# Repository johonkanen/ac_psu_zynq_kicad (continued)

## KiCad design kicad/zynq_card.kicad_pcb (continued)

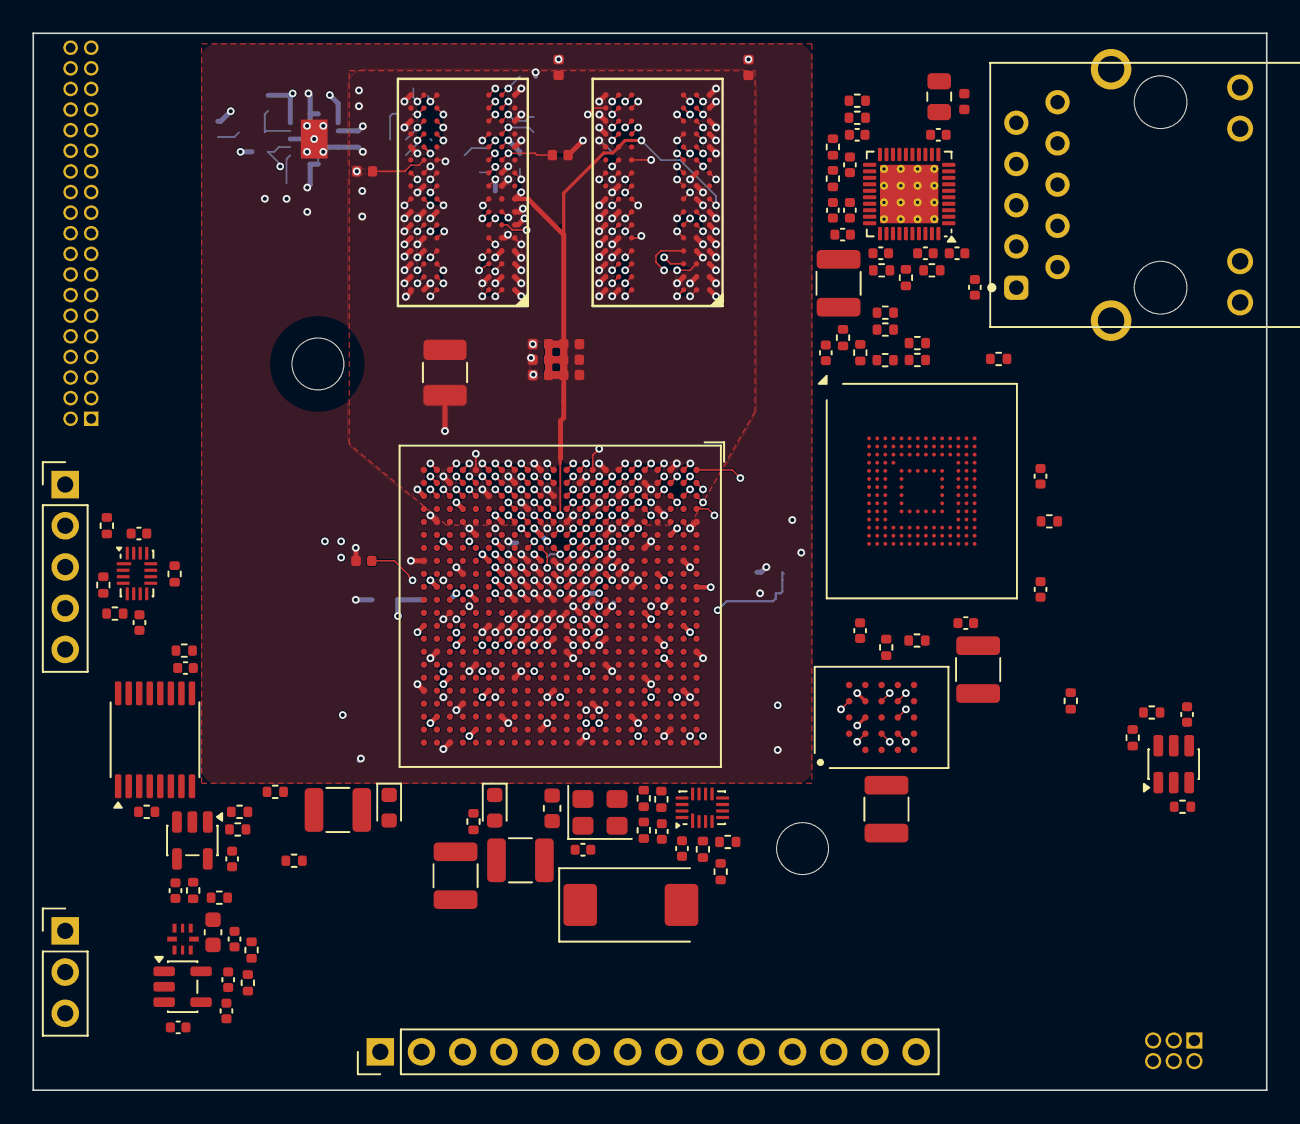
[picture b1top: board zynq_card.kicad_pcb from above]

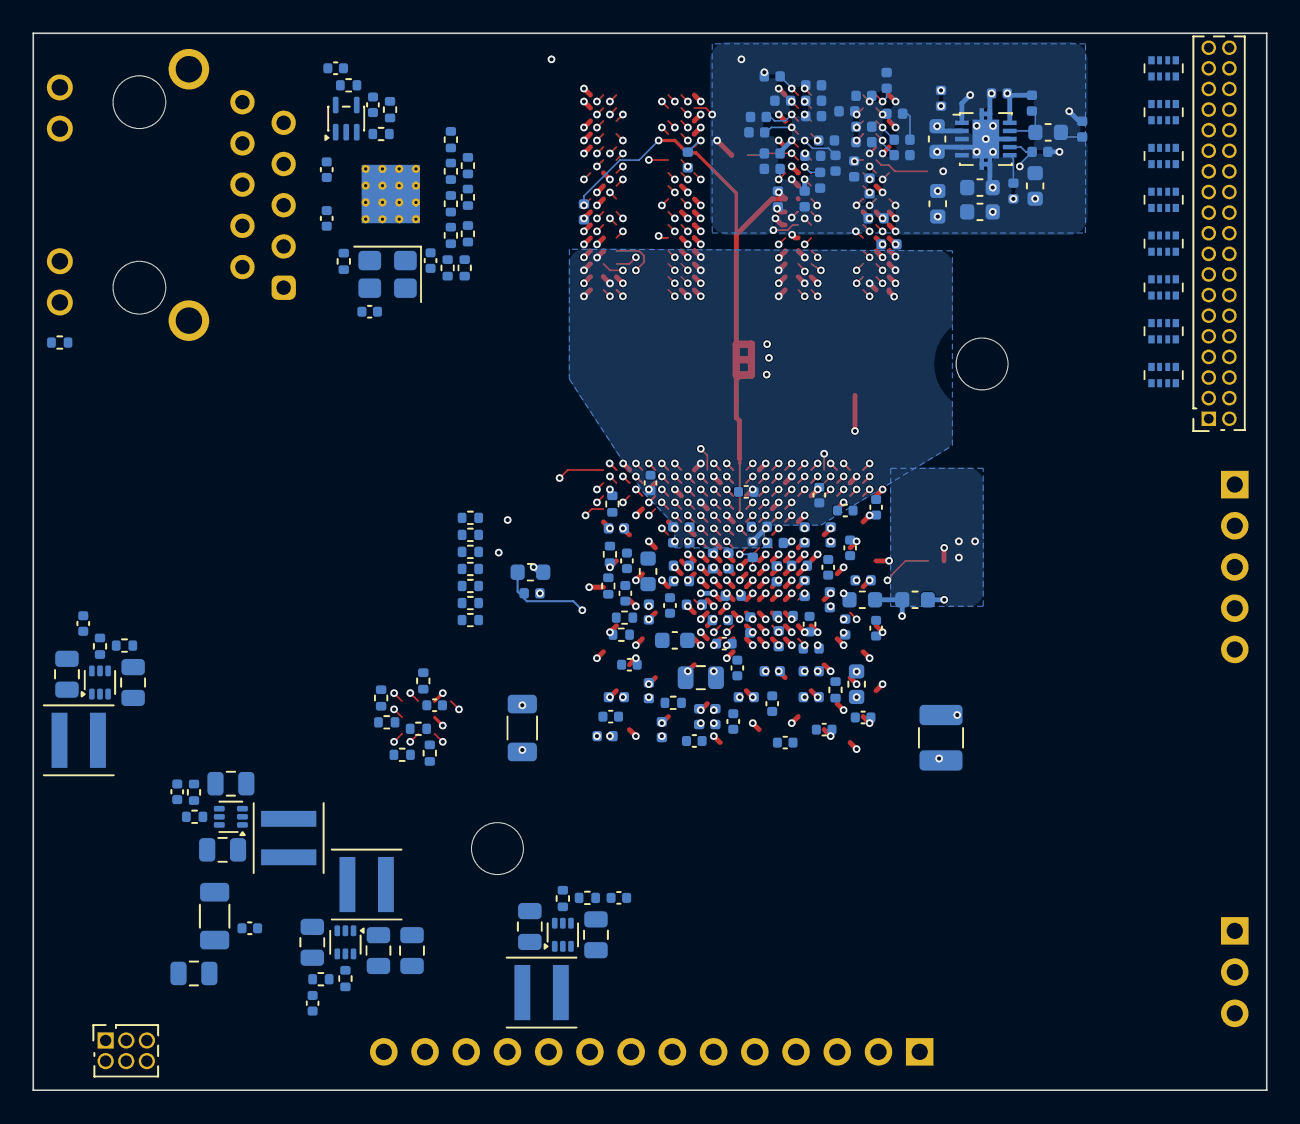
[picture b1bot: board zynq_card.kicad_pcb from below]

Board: 8 copper layers, 76.0 x 65.1 mm, 311 parts (195 on the bottom side), 262 nets.

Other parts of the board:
H1, H2: MountingHole_3.2mm_M3

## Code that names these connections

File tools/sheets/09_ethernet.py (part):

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Ported from the Ti135 card (efinix_soc_board/tools/sheets/09_ethernet.py): same circuit, parts and refs. Checked
against the Realtek RTL8211F(I)/FD(I) data sheet Rev. 1.7:
- One 3.3 V supply. LDO_OUT (pin 30, FD(I) = LDO, no inductor) feeds only AVDD10/DVDD10, caps only.
- RGMII and MDIO pads run from the internal pad LDO at 1.8 V: CFG_EXT (LED0) = 0, CFG_LDO[1:0] (LED2, LED1) = 10
  (Table 6, Table 11). DVDD_RG (pin 28) is that LDO's output: caps only. Both MIO banks are 1.8 V, so the RGMII
  levels match: PHY Vih(1.8 V) 1.2 V vs HSTL 1.8 V VOH; PHY Voh >= 0.9 x 1.8 V vs the HSTL receivers on
  PS_MIO_VREF 0.9 V (sheet 6). Table 58: MDIO also runs at the RGMII pad voltage; every other pin is 3.3 V.
- INTB (pin 31) is open drain (Table 4: O/OD, "supports 3.3 V pull-up"), so R930 pulls it up to 1V8 for MIO10:
  Vol 0.4 V max < MIO VIL 0.63 V (DS187, LVCMOS18). This closes the INTB-level item of ZYNQ_PCB_NOTES.md §8.
- Straps 4k7 (Table 11: an external pull is required): PHYAD = 001 (RXD3 up, RXC/RXCTL down), PLLOFF 0, TXDLY 0,
  RXDLY 1 (the chip defaults). Linux realtek.c sets both RGMII delays from phy-mode = "rgmii-id" anyway.
- PHYRSTB: VIH 2.0 V (3.3 V pin), so eth_rst_n (MIO9, 1.8 V) drives it through U902 (74LVC1G07, open drain,
  R932 10 k to 3V3). R933 holds eth_rst_n low -> PHY in reset until software releases it (>= 10 ms low, 7.17).
  R933 is 1 k, not the Ti135 10 k: the MIO pull-up is on at reset (up to 220 uA at 1.8 V, DS187 IRPU), and
  1 k keeps the node at <= 0.22 V, below the 74LVC1G07 VIL (0.35 x VCC). Driven high it costs 1.8 mA.
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
UX, UY = g(120), g(90)
u = sh.place("RTL8211FD", "U901", UX, UY, value="RTL8211FDI-CG", fields={"LCSC": "C692886"})
P = {11: ("label", "phy_avdd33"), 40: ("label", "phy_avdd33"), 29: ("power", "3V3"),
     3: ("label", "phy_vdd10"), 8: ("label", "phy_vdd10"), 38: ("label", "phy_vdd10"), 21: ("label", "phy_vdd10"),
     30: ("label", "phy_vdd10"), 28: ("label", "phy_dvdd_rg"), 41: ("power", "GND"),
     35: ("nc", None), 39: ("label", "phy_rset"), 36: ("label", "phy_xi"), 37: ("label", "phy_xo"),
     1: ("label", "eth_mdi_a_P"), 2: ("label", "eth_mdi_a_N"), 4: ("label", "eth_mdi_b_P"), 5: ("label", "eth_mdi_b_N"),
     6: ("label", "eth_mdi_c_P"), 7: ("label", "eth_mdi_c_N"), 9: ("label", "eth_mdi_d_P"), 10: ("label", "eth_mdi_d_N"),
     18: ("label", "phy_txd0"), 17: ("label", "phy_txd1"), 16: ("label", "phy_txd2"), 15: ("label", "phy_txd3"),
     19: ("label", "phy_tx_ctl"), 20: ("label", "phy_txc"),
     25: ("label", "phy_rxd0"), 24: ("label", "phy_rxd1"), 23: ("label", "phy_rxd2"), 22: ("label", "phy_rxd3"),
     26: ("label", "phy_rx_ctl"), 27: ("label", "phy_rxc"),
     13: ("hlabel", "mdc"), 14: ("hlabel", "mdio"), 31: ("hlabel", "eth_int_n"), 12: ("label", "phy_rstb"),
     32: ("label", "phy_led0"), 33: ("label", "phy_led1"), 34: ("label", "eth_led_k")}
SHAPE = {"mdc": "input", "mdio": "bidirectional", "eth_int_n": "output"}
for pin, (kind, name) in P.items():
    attach(sh, u, pin, kind, name, n=4, shape=SHAPE.get(name, "passive"))
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
# reset level shift: eth_rst_n (1.8 V, MIO9) -> U902 open drain -> PHYRSTB (3.3 V input, VIH 2.0 V)
b = sh.place("74LVC1G07", "U902", g(90), g(158), value="74LVC1G07GW", fields={"LCSC": "C282345"})
attach(sh, b, "2", "hlabel", "eth_rst_n", 10, shape="input")
attach(sh, b, "4", "label", "phy_rstb", 4)
attach(sh, b, "5", "power", "1V8", 2)
attach(sh, b, "3", "power", "GND", 2)
attach(sh, b, "1", "nc")
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_, rt, rb = vert2(sh, "R", "R933", rn[0], rn[1] + g(5), "1k", text="right")
sh.wire(rn, rt); sh.junction(*rn)
sh.wire(rb, down(rb, 2)); power_at(sh, "GND", down(rb, 2), "down")
for ref, x, top in (("C901", g(122), ("label", "phy_rstb")), ("C951", g(130), ("power", "1V8"))):
    _, ct, cb = vert2(sh, "C", ref, x, g(156), "100n", text="right")
    sh.wire(ct, up(ct, 2))
    if top[0] == "label":
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
# crystal
y = sh.place("Crystal_GND24", "Y901", g(110), g(186), value="25MHz")
attach(sh, y, "1", "label", "phy_xi", 3)
attach(sh, y, "3", "label", "phy_xo", 3)
for pin in ("2", "4"):
    attach(sh, y, pin, "power", "GND", 2)
for k, net in enumerate(("phy_xi", "phy_xo")):
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yy = g(184)
_, a, bb = horiz2(sh, "FerriteBead_Small", "FB901", g(30), yy, "BLM15PX121SN1D", text="above")
sh.wire(a, left(a, 2)); power_at(sh, "3V3", left(a, 2), "left")
node = right(bb, 4); sh.wire(bb, node); sh.label("phy_avdd33", *right(node, 16), 0)
sh.wire(node, right(node, 16))
for j, (val, fp) in enumerate((("10u", C0805), ("100n", None), ("100n", None))):
    cx = node[0] + j * g(6)
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sh.text("AVDD33 (pins 11, 40) through a ferrite: 10u + 2 x 100n", g(14), g(174))

# PHY decoupling
label_caps(g(200), g(150), "phy_vdd10", [("C930", "1u", None)] + [(f"C9{31 + i}", "100n", None) for i in range(4)],
           "LDO_OUT 1.0 V -> AVDD10 (3, 8, 38) + DVDD10 (21) only:\n1u + 4 x 100n (>= 0.1u, Table 9.2)")
label_caps(g(200), g(176), "phy_dvdd_rg", [("C935", "1u", None), ("C936", "100n", None)],
           "DVDD_RG: RGMII pad LDO output (1.8 V), caps only")
cap_row(sh, g(252), g(176), "3V3", [("C940", "1u", None), ("C941", "100n", None)], "DVDD33 (pin 29)")

# magjack HanRun HR911130A (LCSC C54408, chosen 2026-10-25 for stock; MECHANICAL.md J9)
J = sh.place("HR911130A", "J9", g(260), g(90), value="HR911130A", fields={"LCSC": "C54408"})
for pin, net in (("2", "eth_mdi_a_P"), ("3", "eth_mdi_a_N"), ("4", "eth_mdi_b_P"), ("7", "eth_mdi_b_N"),
                 ("5", "eth_mdi_c_P"), ("6", "eth_mdi_c_N"), ("8", "eth_mdi_d_P"), ("9", "eth_mdi_d_N")):
    attach(sh, J, pin, "label", net, 4)
attach(sh, J, "1", "label", "eth_ct", 4)
attach(sh, J, "10", "power", "GND", 3)
attach(sh, J, "SH", "power", "GND", 3)
attach(sh, J, "11", "label", "eth_led_a", 4)
attach(sh, J, "12", "label", "eth_led_k", 4)
attach(sh, J, "14", "nc")
attach(sh, J, "13", "nc")
_, ct, cb = vert2(sh, "C", "C950", g(258), g(130), "100n", text="right")
sh.wire(ct, up(ct, 2)); sh.label("eth_ct", *up(ct, 2), 90)
sh.wire(cb, down(cb, 2)); power_at(sh, "GND", down(cb, 2), "down")
pull_r(sh, "R950", g(268), g(130), "eth_led_a", "3V3", "330R")
sh.text("Jack LED: green anode via R950 to 3V3, cathode on PHY LED2 (3.3 V pin, active low with its CFG_LDO1\n"
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
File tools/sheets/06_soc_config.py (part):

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        "their pull-ups sit with the parts on their sheets. JTAG J1 is 3.3 V (FTDI mini-module), shifted by U601.",
        g(10), g(14))  # noqa: F405

# ---------------------------------------------------------------- unit 6: bank 500 (QSPI, straps, GPIO, PS_CLK/POR)
MIO0 = {"A1": ("qspi_cs_n", "output"), "A2": ("qspi_io0", "bidirectional"), "F6": ("qspi_io1", "bidirectional"),
        "E4": ("qspi_io2", "bidirectional"), "A3": ("qspi_io3", "bidirectional"), "A4": ("qspi_sclk", "output"),
        "D5": ("emmc_rst_n", "output"), "C4": ("eth_rst_n", "output"), "G7": ("eth_int_n", "input"),
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    if ball in MIO0:
        attach(sh, u6, ball, "hlabel", MIO0[ball][0], n=8, shape=MIO0[ball][1], side="left")  # noqa: F405
    elif ball == "E5":  # MIO8: QSPI feedback clock, only its strap (keep the stub < 10 mm)
        attach(sh, u6, ball, "label", "qspi_fbclk", n=8, side="left")  # noqa: F405
    elif ball in ("B3", "C6"):  # VCCO_MIO0 (stacked)
        if ball == "B3":
            attach(sh, u6, ball, "power", "1V8", n=4, side="left")  # noqa: F405
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        else:  # 28-39 (USB0, unused), 46, 47
            attach(sh, u7, ball, "nc")  # noqa: F405
    elif name == "PS_MIO_VREF_501":
        attach(sh, u7, ball, "label", "ps_mio_vref", n=8, side="left")  # noqa: F405
    elif name == "PS_SRST_B_501":
        attach(sh, u7, ball, "label", "ps_srst_n", n=8, side="left")  # noqa: F405
    elif ball == "A10":  # VCCO_MIO1 (stacked)
        attach(sh, u7, ball, "power", "1V8", n=4, side="left")  # noqa: F405
sh.text("MIO28-39 (USB0), 46, 47: spare", g(148), g(150))  # noqa: F405
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c_vref = ref("C")
_, ct, cb = vert2(sh, "C", c_vref, VX + g(18), VY, "10n", text="right")  # noqa: F405
set_field(sh, c_vref, "Footprint", C0402)  # noqa: F405
sh.wire(ct, up(ct, 2)); sh.label("ps_mio_vref", *up(ct, 2), 90)  # noqa: F405
sh.wire(cb, down(cb, 2)); power_at(sh, "GND", down(cb, 2), "down")  # noqa: F405
fx = VX + g(26)  # noqa: F405
sh.label("ps_mio_vref", fx, VY - g(4), 90); sh.wire((fx, VY - g(4)), (fx, VY)); sh.pwr_flag(fx, VY, 180)  # noqa: F405
pull("ps_srst_n", "1V8", "10k", VX + g(34), VY)  # noqa: F405

# ---------------------------------------------------------------- unit 1: bank 0
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         "G9": ("power", "GND"), "M12": ("power", "GND"), "L11": ("power", "GND"), "L12": ("power", "GND"),
         "M11": ("power", "GND"), "T7": ("power", "1V8"), "T8": ("power", "1V8"), "T10": ("power", "1V8"),
         "K11": ("power", "1V8"), "R12": ("power", "1V8"), "G10": ("nc", None),
         "T12": ("label", "cfg_done"), "T14": ("label", "cfg_init_n"), "T11": ("label", "cfg_program_n"),
         "G11": ("label", "jtag_tck_1v8"), "H13": ("label", "jtag_tdi_1v8"), "G14": ("label", "jtag_tdo_1v8"),
         "G12": ("label", "jtag_tms_1v8")}
u1 = place_unit(sh, "XC7Z020-CLG484", "U20", g(290), g(30), 1)  # noqa: F405
for ball, (kind, net) in UNIT1.items():
    attach(sh, u1, ball, kind, net, n=6, side="left")  # noqa: F405
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set_field(sh, "U601", "Footprint", "Package_DFN_QFN:UQFN-16_1.8x2.6mm_P0.4mm")  # noqa: F405
for pin, kind, net in ((14, "power", "3V3"), (15, "power", "3V3"), (16, "power", "3V3"), (5, "power", "3V3"),
                       (6, "power", "GND"), (7, "power", "GND"), (8, "power", "GND"), (13, "power", "1V8"),
                       (1, "label", "jtag_tck"), (2, "label", "jtag_tdi"), (3, "label", "jtag_tms"),
                       (4, "label", "jtag_tdo"), (12, "label", "jtag_tck_1v8"), (11, "label", "jtag_tdi_1v8"),
                       (10, "label", "jtag_tms_1v8"), (9, "label", "jtag_tdo_1v8")):
    attach(sh, u, pin, kind, net, n=4)  # noqa: F405
decap("3V3", JX - g(14), JY + g(24))  # noqa: F405
decap("1V8", JX + g(20), JY + g(24))  # noqa: F405
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
j1 = sh.place("Conn_01x05", "J1", g(318), g(178), value="JTAG 3V3")  # noqa: F405
set_field(sh, "J1", "Footprint", "Connector_PinHeader_2.54mm:PinHeader_1x05_P2.54mm_Vertical")  # noqa: F405
for pin, net in ((1, "jtag_tdi"), (2, "jtag_tck"), (3, "jtag_tms"), (4, "jtag_tdo")):
    p = j1.pin(pin)
    sh.wire(p, left(p, 6)); sh.label(net, *left(p, 6), 180)  # noqa: F405
p = j1.pin(5)
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
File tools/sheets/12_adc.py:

#!/usr/bin/env python3
"""Sheet 12 (adc): 8:1 mux -> unity-gain buffer -> ADS7056 (14 bit, 2.5 MSPS).

Ported from the Ti135 card (efinix_soc_board/tools/sheets/13_adc.py, its parts and symbols), whose front end comes
from the Agilex 3 card (~/dev/ti60f225_control_card docs/design-notes.md, "ADC front end for 2.5 MSPS"):
- U1201 SN74LV4051APWR (C7793) on 3V3_analog (U341, sheet 3). TI SCLS428K: the 4051 pinout of the CD4051B symbol,
  pins 7 and 8 both GND (the symbol's VEE pin goes to GND), logic inputs VIH = 0.7 VCC = 2.31 V at 3.3 V and
  5.5 V tolerant, so adbsel0-2 come straight from bank 33 (3.3 V; the Ti135 card needed translators). INH to GND.
  X0 = GND as a zero reference.
- U1202 OPA365 buffer (50 MHz; the ADS7056 kickback RC needs UGB >= 28 MHz).
- Kickback RC at AINP: 33 R + 680 p C0G (ADS7056 data sheet 2.5 MSPS design).
- U1203 ADS7056: AVDD = reference, 4u7 0603 + 100 n at the pin, from 3V3_analog. DVDD = 3V3 (ZYNQ_PCB_NOTES.md §4.4:
  SPI straight to the 3.3 V bank 33; SBAS769: DVDD 1.65-3.6 V, independent of AVDD). The Ti135 card had DVDD at 1V8.
- CS / SCLK / SDO 33 R series (60 MHz SCLK). Capture SDO with a phase-shifted clock (design note).
Mux inputs: X1/X2/X3/X5 monitor card rails 1V0, 1V8, 3V3/2, 1V35 (the Ti135 VCORE, 1V8, 3V3/2, 1V1);
X4/X6/X7 = isoada2/3/1 from J3 (sheet 13).
Port names are sheet 11's: adc_cs_n, adc_sclk, adc_sdo, adbsel0-2.
"""
from _common import *  # noqa: F401,F403

sh = sheet("12_adc.kicad_sch")  # noqa: F405
sh.text("ADC chain: mux U1201 -> buffer U1202 -> ADS7056 U1203 (Ti135 sheet 13; front end as on the Agilex 3 card, 2.5 MSPS).\n"
        "Mux: X0 GND (zero ref), X1 1V0, X2 1V8, X3 3V3/2, X4 isoada2, X5 1V35, X6 isoada3, X7 isoada1.\n"
        "Full scale 0..3.3 V (AVDD = reference, 3V3_analog). DVDD on 3V3: SPI and selects straight to bank 33.",
        g(14), g(14))  # noqa: F405

# mux (SN74LV4051A, CD4051B symbol: same pinout, pin 7 = GND on the TI part)
m = sh.place("CD4051B", "U1201", g(80), g(80), value="SN74LV4051APWR", fields={"LCSC": "C7793"})
attach(sh, m, "13", "power", "GND", 3)  # X0 = zero reference  # noqa: F405
for pin, net in (("14", "mon_1v0"), ("15", "mon_1v8"), ("12", "mon_3v3"), ("1", "isoada2"),
                 ("5", "mon_1v35"), ("2", "isoada3"), ("4", "isoada1")):
    attach(sh, m, pin, "hlabel" if net.startswith("isoada") else "label", net, 4)  # noqa: F405
for pin, net in (("11", "adbsel0"), ("10", "adbsel1"), ("9", "adbsel2")):
    attach(sh, m, pin, "hlabel", net, 4, shape="input")  # noqa: F405
for pin in ("6", "7", "8"):
    attach(sh, m, pin, "power", "GND", 3)  # noqa: F405
attach(sh, m, "16", "power", "3V3_analog", 3)  # noqa: F405
attach(sh, m, "3", "label", "adc_mux_out", 4)  # noqa: F405
cap_row(sh, g(60), g(120), "3V3_analog", [("C1201", "1u", None)], "U1201 VCC")  # noqa: F405
sh.text("SN74LV4051A (SCLS428K): pins 7/8 GND; VIH 2.31 V at 3.3 V", g(56), g(56))  # noqa: F405

# rail monitors (series R limits the current into the mux)
sh.text("Rail monitors", g(14), g(140))  # noqa: F405
for k, (rail, net, val) in enumerate((("1V0", "mon_1v0", "100R"), ("1V8", "mon_1v8", "1k"),
                                      ("3V3", "mon_3v3", "1k"), ("1V35", "mon_1v35", "1k"))):
    pull_r(sh, f"R12{k + 1:02d}", g(18) + k * g(8), g(152), net, rail, val)  # noqa: F405
pull_r(sh, "R1205", g(18) + 4 * g(8), g(152), "mon_3v3", "GND", "1k")  # noqa: F405
sh.text("3V3 via 1k/1k divider", g(46), g(166))  # noqa: F405

# buffer
b = sh.place("OPA365xxDBV", "U1202", g(160), g(80), value="OPA365AIDBVR", fields={"LCSC": "C96626"})
attach(sh, b, "3", "label", "adc_mux_out", 4)  # noqa: F405
out = b.pin("1")
nin = b.pin("4")
node = right(out, 4)  # noqa: F405
sh.wire(out, node)
sh.wire(nin, (nin[0], nin[1] + g(4)), (node[0], nin[1] + g(4)), node)  # noqa: F405
sh.junction(*node)
attach(sh, b, "5", "power", "3V3_analog", 2)  # noqa: F405
attach(sh, b, "2", "power", "GND", 2)  # noqa: F405
_, a, r = horiz2(sh, "R", "R1206", node[0] + g(6), node[1], "33R", text="above")  # noqa: F405
sh.wire(node, a)
ainp = right(r, 4)  # noqa: F405
sh.wire(r, ainp)
_, ct, cb = vert2(sh, "C", "C1202", ainp[0], ainp[1] + g(5), "680p C0G", text="right")  # noqa: F405
sh.wire(ainp, ct); sh.junction(*ainp)
sh.wire(cb, down(cb, 2)); power_at(sh, "GND", down(cb, 2), "down")  # noqa: F405
sh.wire(ainp, right(ainp, 4)); sh.label("adc_ainp", *right(ainp, 4), 0)  # noqa: F405
cap_row(sh, g(150), g(120), "3V3_analog", [("C1203", "100n", None)], "U1202 V+")  # noqa: F405

# ADC
a7 = sh.place("ADS7056", "U1203", g(250), g(80), value="ADS7056IRUGR", fields={"LCSC": "C2669798"})
set_field(sh, "U1203", "Footprint", "zynq_card:ads7056")  # noqa: F405
attach(sh, a7, "7", "label", "adc_ainp", 4)  # noqa: F405
attach(sh, a7, "8", "power", "GND", 3)  # noqa: F405
attach(sh, a7, "5", "power", "GND", 3)  # noqa: F405
attach(sh, a7, "6", "power", "3V3_analog", 3)  # noqa: F405
attach(sh, a7, "4", "power", "3V3", 7)  # noqa: F405
for pin, net in (("1", "adc_cs_n_r"), ("3", "adc_sclk_r"), ("2", "adc_sdo_r")):
    attach(sh, a7, pin, "label", net, 4)  # noqa: F405
cap_row(sh, g(230), g(120), "3V3_analog", [("C1204", "4u7", "Capacitor_SMD:C_0603_1608Metric"), ("C1205", "100n", None)],  # noqa: F405
        "AVDD = reference: 4u7 0603 + 100n at the pin")
cap_row(sh, g(290), g(120), "3V3", [("C1206", "1u", None)], "DVDD 3V3")  # noqa: F405
sh.text("SPI series 33 R (60 MHz SCLK); DVDD 3V3 = bank 33", g(220), g(140))  # noqa: F405
for k, (soc, local, shape) in enumerate((("adc_cs_n", "adc_cs_n_r", "input"), ("adc_sclk", "adc_sclk_r", "input"),
                                         ("adc_sdo", "adc_sdo_r", "output"))):
    series_r(sh, f"R12{10 + k:02d}", g(240), g(148) + k * g(5), "33R", "hlabel", soc, "label", local, shape)  # noqa: F405

fill_footprints(sh, {"R": R0402, "C": C0402, "CD4051B": "Package_SO:TSSOP-16_4.4x5mm_P0.65mm",  # noqa: F405
                     "OPA365xxDBV": "Package_TO_SOT_SMD:SOT-23-5"})
sh.save()
print("12_adc: U1201-U1203, R1201-R1206, R1210-R1212, C1201-C1206")

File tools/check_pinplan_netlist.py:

#!/usr/bin/env python3
"""Phase-2 closing check: every PL pin-plan signal and every MIO signal sits on its U20 ball in the netlist, and the
net reaches the part at the far end.

    tools/check_pinplan_netlist.py      (after tools/build_schematic.sh, which exports work/zynq_card_net.xml)

- PL: vivado/pinplan/zynq_pinplan.csv (signal -> ball). The net on that ball must carry the signal's name, and the far
  end is J3.<n> from the note column (j3), J5.<n> (lcd, the sheet-13 order), the ADC parts (adc) or the LED (led).
- MIO: MIO number -> ball from the XC7Z020-CLG484 symbol pin names (PS_MIO<n>_50x), checked against
  vivado/pinplan/ps7_mio.csv (Vivado's PS7 settings); the expected net and far-end pad per MIO are below.
  Every other MIO ball must be unconnected.
"""
import csv
import os
import sys
import xml.etree.ElementTree as ET

TOOLS = os.path.dirname(os.path.abspath(__file__))
ROOT = os.path.dirname(TOOLS)
sys.path.insert(0, os.path.join(TOOLS, "p2k"))
from p2k.sexpr import find, find_all, load  # noqa: E402

NET = os.path.join(ROOT, "work", "zynq_card_net.xml")
LIB = os.path.join(ROOT, "lib", "zynq_card.kicad_sym")
PP = os.path.join(ROOT, "vivado", "pinplan", "zynq_pinplan.csv")
PS7 = os.path.join(ROOT, "vivado", "pinplan", "ps7_mio.csv")

LCD = ["t_irq", "t_do", "t_din", "t_cs_n", "t_clk", "lcd_mosi", "lcd_led", "lcd_sck", "lcd_miso",
       "lcd_dc", "lcd_reset_n", "lcd_cs_n"]  # J5 pins 1-12 (sheet 13)
PL_FAR = {"adc_cs_n": ("R1210", "1"), "adc_sclk": ("R1211", "1"), "adc_sdo": ("R1212", "1"),
          "adbsel0": ("U1201", "11"), "adbsel1": ("U1201", "10"), "adbsel2": ("U1201", "9"),
          "led0_n": ("D1101", None), "led1_n": ("D1102", None),
          **{s: ("J5", str(i)) for i, s in enumerate(LCD, 1)}}
LOCAL = {"led0_n": "/11 soc_pl/led0_n", "led1_n": "/11 soc_pl/led1_n"}

# MIO: (net, far-end ref, pin or None, ps7_mio.csv peripheral)
MIO = {1: ("qspi_cs_n", "U801", "C2", "Quad SPI Flash"), 2: ("qspi_io0", "U801", "D3", "Quad SPI Flash"),
       3: ("qspi_io1", "U801", "D2", "Quad SPI Flash"), 4: ("qspi_io2", "U801", "C4", "Quad SPI Flash"),
       5: ("qspi_io3", "U801", "D4", "Quad SPI Flash"), 6: ("qspi_sclk", "U801", "B2", "Quad SPI Flash"),
       7: ("emmc_rst_n", "U1001", "K5", "GPIO"), 8: ("/06 soc_config/qspi_fbclk", "R607", None, "Quad SPI Flash"),
       9: ("eth_rst_n", "U902", "2", "GPIO"), 10: ("eth_int_n", "U901", "31", "GPIO"),
       16: ("rgmii_txc", "R901", None, "Enet 0"), 17: ("rgmii_txd0", "R903", None, "Enet 0"),
       18: ("rgmii_txd1", "R904", None, "Enet 0"), 19: ("rgmii_txd2", "R905", None, "Enet 0"),
       20: ("rgmii_txd3", "R906", None, "Enet 0"), 21: ("rgmii_tx_ctl", "R902", None, "Enet 0"),
       22: ("rgmii_rxc", "R907", None, "Enet 0"), 23: ("rgmii_rxd0", "R909", None, "Enet 0"),
       24: ("rgmii_rxd1", "R910", None, "Enet 0"), 25: ("rgmii_rxd2", "R911", None, "Enet 0"),
       26: ("rgmii_rxd3", "R912", None, "Enet 0"), 27: ("rgmii_rx_ctl", "R908", None, "Enet 0"),
       40: ("sd_clk", "R1001", None, "SD 0"), 41: ("sd_cmd", "U1001", "M5", "SD 0"),
       42: ("sd_dat0", "U1001", "A3", "SD 0"), 43: ("sd_dat1", "U1001", "A4", "SD 0"),
       44: ("sd_dat2", "U1001", "A5", "SD 0"), 45: ("sd_dat3", "U1001", "B2", "SD 0"),
       48: ("uart_tx", "U1301", "11", "UART 1"), 49: ("uart_rx", "U1301", "12", "UART 1"),
       50: ("i2c_scl", "R1305", None, "I2C 0"), 51: ("i2c_sda", "R1306", None, "I2C 0"),
       52: ("mdc", "U901", "13", "Enet 0"), 53: ("mdio", "U901", "14", "Enet 0")}


def main():
    x = ET.parse(NET).getroot()
    net_of, nodes = {}, {}
    for n in x.iter("net"):
        ns = {(d.get("ref"), d.get("pin")) for d in n.iter("node")}
        nodes[n.get("name")] = ns
        for k in ns:
            net_of[k] = n.get("name")
    fails = []

    def check(what, ball, want, ref, pin):
        got = net_of.get(("U20", ball))
        want = want if want.startswith("/") else "/" + want
        if got != want:
            fails.append(f"{what}: U20.{ball} on {got}, want {want}")
        elif not any(r == ref and (pin is None or p == pin) for r, p in nodes[got]):
            fails.append(f"{what}: {got} does not reach {ref}{'.' + pin if pin else ''}")

    with open(PP) as f:
        pl = list(csv.DictReader(f))
    for r in pl:
        s = r["signal"]
        if r["group"] == "j3":
            far = ("J3", r["note"].split(".")[1])
        else:
            far = PL_FAR[s]
        check(f"PL {s}", r["ball"], LOCAL.get(s, s), *far)

    sym = next(s for s in find_all(load(LIB), "symbol") if s[1] == "XC7Z020-CLG484")
    ball = {}
    for sub in find_all(sym, "symbol"):
        for p in find_all(sub, "pin"):
            name = find(p, "name")[1]
            if name.startswith("PS_MIO") and name[6:].split("_")[0].isdigit():
                ball[int(name[6:].split("_")[0])] = find(p, "number")[1]
    assert len(ball) == 54, len(ball)
    with open(PS7) as f:
        ps7 = {int(r[0]): r[1] for r in csv.reader(f) if r and r[0].isdigit()}
    for mio, b in sorted(ball.items()):
        if mio in MIO:
            net, ref, pin, periph = MIO[mio]
            if ps7.get(mio) != periph:
                fails.append(f"MIO{mio}: ps7_mio.csv has {ps7.get(mio)!r}, want {periph!r}")
            check(f"MIO{mio}", b, net, ref, pin)
        else:
            got = net_of.get(("U20", b))
            if got and not got.startswith("unconnected-"):
                fails.append(f"MIO{mio} (spare): U20.{b} on {got}")
    for f_ in fails:
        print("FAIL", f_)
    print(f"check_pinplan_netlist: {len(pl)} PL signals, {len(MIO)} MIO signals, "
          f"{54 - len(MIO)} spare MIO open; {len(fails)} failures")
    return 1 if fails else 0


if __name__ == "__main__":
    sys.exit(main())

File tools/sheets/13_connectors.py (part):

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  MECHANICAL.md). Every digital J3 net has the sheet-11 name (zynq_pinplan.csv); the script checks each pin number
  against the pin plan's note column. 10 k pull-downs on all 32 digital pins (8 x 4D02WGJ0103TCE, C25725): with
  PUDC_B high (sheet 11) the PL has no pull-ups during configuration, so the baseboard sees low until the bitstream
  drives the pins (STATUS.md "J3 safe state", ZYNQ_PCB_NOTES.md §5). ISOADA1-3 are analog inputs to the mux
  (sheet 12): no pull-down, it would load the source. ISOGND = GND, pin 38 NC.
- J5: LCD/touch header, the Ti135 sheet 14 pinout (Ti60 J4), lcd_*/t_* straight from bank 33 (3.3 V).
- J2: UART console, family pinout (1 = RX into the SoC, 2 = TX, 3 = GND), 1 k series as on the Ti135 card.
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set_field(sh, "U1301", "Footprint", "Package_DFN_QFN:UQFN-16_1.8x2.6mm_P0.4mm")  # noqa: F405
for pin, kind, net in ((14, "power", "3V3"), (15, "power", "3V3"), (16, "power", "GND"), (5, "power", "3V3"),
                       (6, "power", "3V3"), (7, "power", "GND"), (8, "power", "GND"), (13, "power", "1V8"),
                       (1, "label", "uart_rx_3v3"), (2, "label", "uart_tx_3v3"),
                       (3, "power", "GND"), (4, "power", "GND"), (10, "nc", None), (9, "nc", None)):
    attach(sh, u, pin, kind, net, n=4)  # noqa: F405
hlabel_right(sh, "uart_rx", u.pin(12), 6, "output")  # noqa: F405
hlabel_right(sh, "uart_tx", u.pin(11), 6, "input")  # noqa: F405
cap_row(sh, TX - g(14), TY + g(26), "3V3", [("C1301", "100n", None)], "VCCA")  # noqa: F405
cap_row(sh, TX + g(20), TY + g(26), "1V8", [("C1302", "100n", None)], "VCCB")  # noqa: F405

j2 = sh.place("Conn_01x03", "J2", g(130), g(160), value="UART 3V3")
set_field(sh, "J2", "Footprint", "Connector_PinHeader_2.54mm:PinHeader_1x03_P2.54mm_Vertical")  # noqa: F405
for pin, ref, net, txt in ((1, "R1301", "uart_rx_3v3", "above"), (2, "R1302", "uart_tx_3v3", "below")):
    _, a, b = horiz2(sh, "R", ref, g(116), j2.pin(pin)[1], "1k", text=txt)  # noqa: F405
    sh.wire(b, j2.pin(pin))
    sh.wire(a, left(a, 2)); sh.label(net, *left(a, 2), 180)  # noqa: F405
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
